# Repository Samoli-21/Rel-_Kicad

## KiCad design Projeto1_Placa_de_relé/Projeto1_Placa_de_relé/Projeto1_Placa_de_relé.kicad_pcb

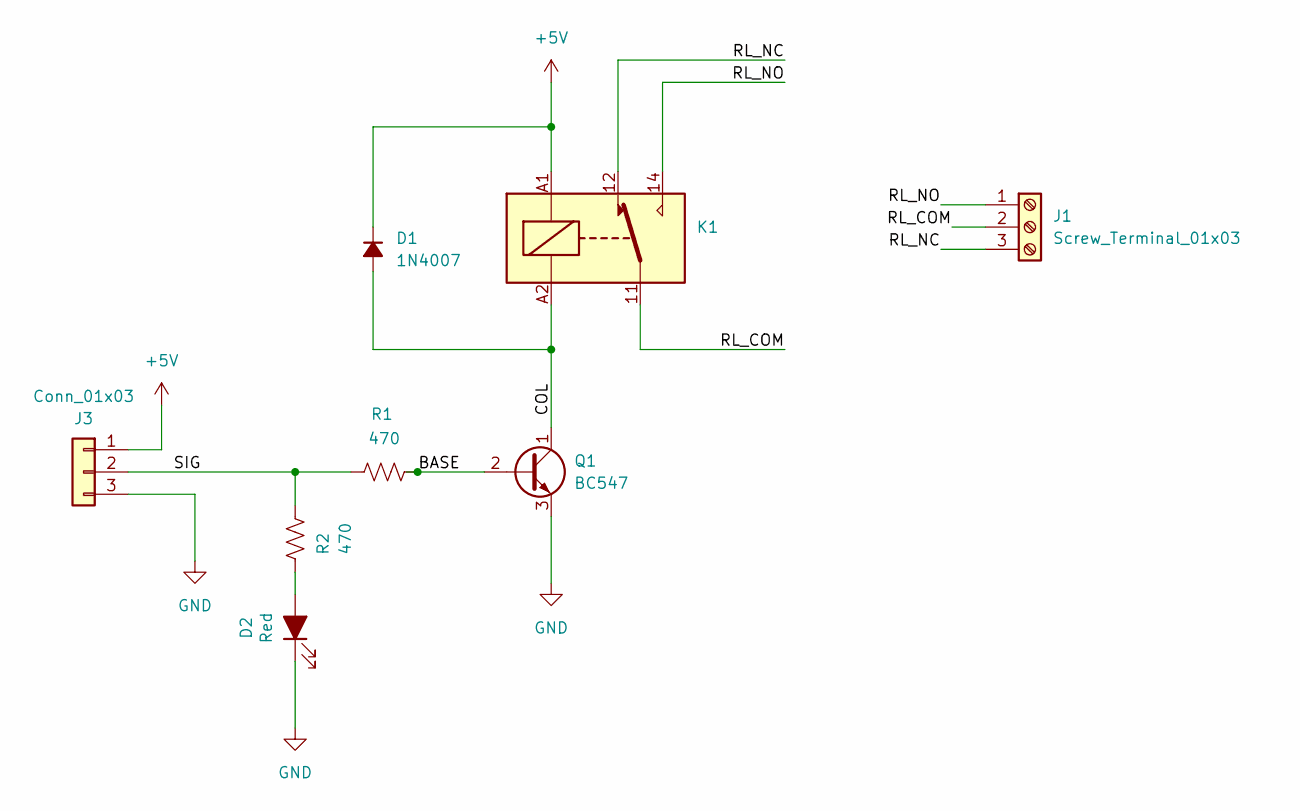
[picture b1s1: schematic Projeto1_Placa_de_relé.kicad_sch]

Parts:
D1: 1N4007; D_DO-41_SOD81_P10.16mm_Horizontal
D2: Red; LED_D5.0mm
J1: Screw_Terminal_01x03; TerminalBlock_Phoenix_MKDS-1,5-3-5.08_1x03_P5.08mm_Horizont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
J3: Conn_01x03; PinSocket_1x03_P2.54mm_Vertical
K1: SRD-05VDC-SC-C; Relay_SPDT_Finder_36.11
Q1: BC547; TO-92_Inline_Wide
R1, R2: 470; R_Axial_DIN0207_L6.3mm_D2.5mm_P10.16mm_Horizontal

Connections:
+5V: D1.1 (K), J3.1, K1.A1
/BASE: Q1.2 (B), R1.2
/COL: D1.2 (A), K1.A2, Q1.1 (C)
/RL_COM: J1.2, K1.11
/RL_NC: J1.3, K1.12
/RL_NO: J1.1, K1.14
/SIG: J3.2, R1.1, R2.1
GND: D2.1 (K), J3.3, Q1.3 (E)
unnamed: D2.2 (A), R2.2

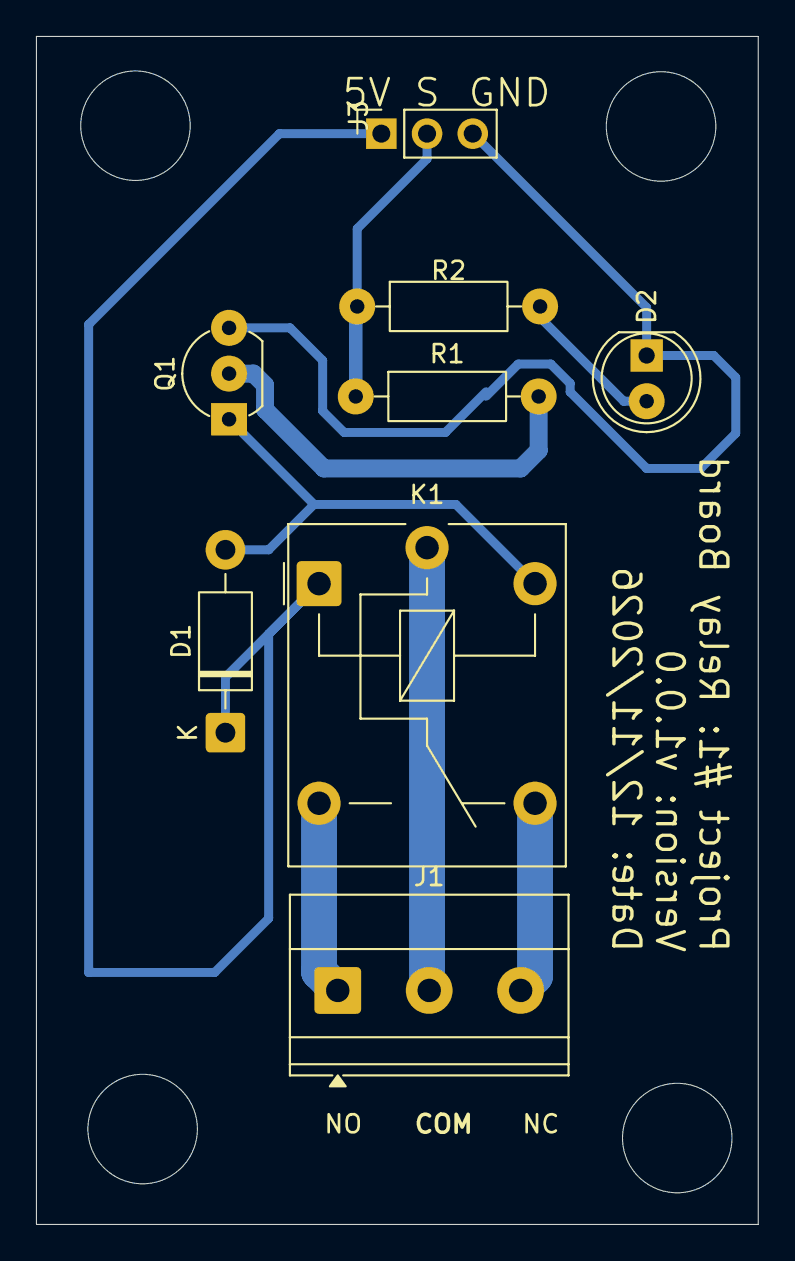
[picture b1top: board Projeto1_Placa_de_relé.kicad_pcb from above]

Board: 2 copper layers, 40.1 x 66.0 mm, 8 parts (0 on the bottom side), 9 nets.
